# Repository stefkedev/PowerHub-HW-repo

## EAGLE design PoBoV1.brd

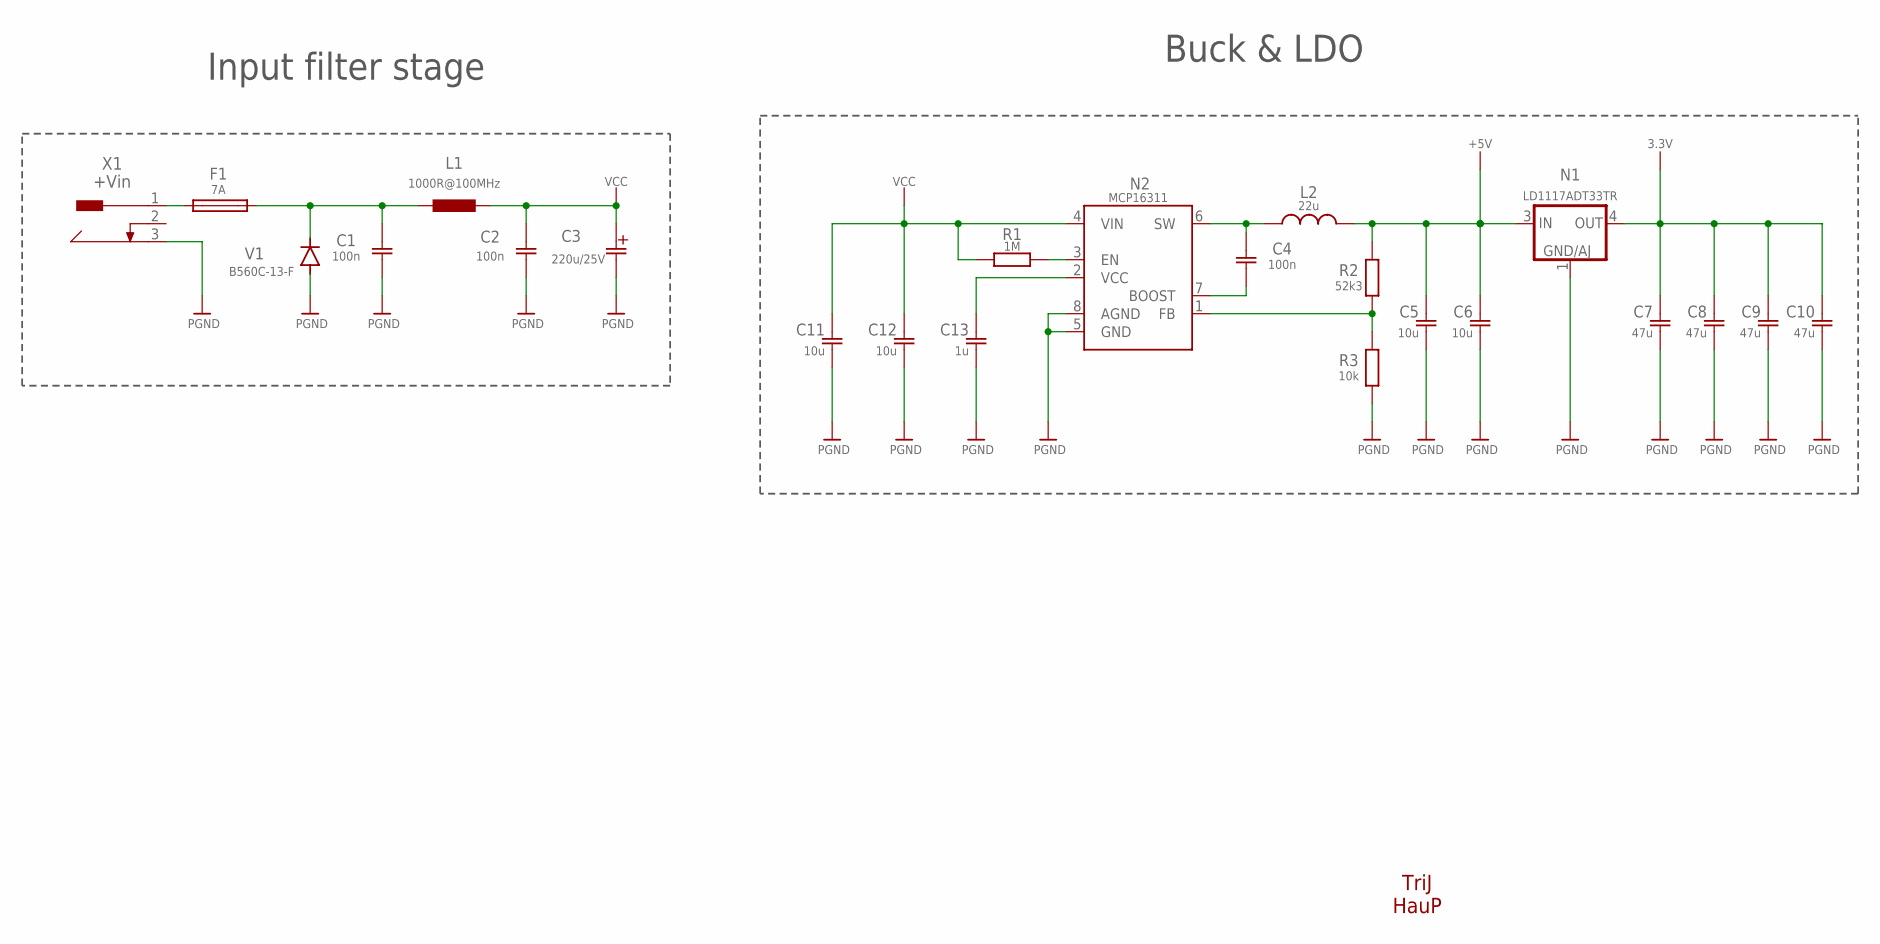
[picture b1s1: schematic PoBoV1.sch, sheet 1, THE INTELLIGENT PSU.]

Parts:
C1, C2, C4: 100n; C0805
C3: 220u/25V; E2,5-6L
C5, C6, C11, C12: 10u; C0805
C7, C8, C9, C10: 47u; C0805
C13: 1u; C0805
F1: 7A; TE5
L1: 1000R@100MHz; 0204/7@1
L2: 22u; WE-TPC_5818/5828
N1: LD1117ADT33TR; DPACK
N2: MCP16311; MSOP8
R1: 1M; R0805
R2: 52k3; R0805
R3: 10k; R0805
V1: B560C-13-F; SMC
X1: +Vin; DCJ0202

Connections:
+3.3: C7.1, C8.1, C9.1, C10.1, N1.4 (OUT); also elsewhere on the board
+5V: C5.1, C6.1, L2.2, N1.3 (IN), R2.2; also elsewhere on the board
unnamed: F1.1, X1.1
unnamed: C4.2, N2.7 (BOOST)
unnamed: N2.3 (EN), R1.2
unnamed: C1.1, F1.2, L1.1, V1.C
unnamed: C4.1, L2.1, N2.6 (SW)
unnamed: N2.1 (FB), R2.1, R3.2
unnamed: C13.1, N2.2 (VCC)
PGND: C1.2, C2.2, C3.-, C5.2, C6.2, C7.2, C8.2, C9.2, C10.2, C11.2, C12.2, C13.2, N1.1 (GND/ADJ), N2.5 (GND), N2.8 (AGND), R3.1, V1.A, X1.3; also elsewhere on the board
VCC: C2.1, C3.+, C11.1, C12.1, L1.2, N2.4 (VIN), R1.1; also elsewhere on the board

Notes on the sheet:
TriJ HauP
Input filter stage
Buck & LDO

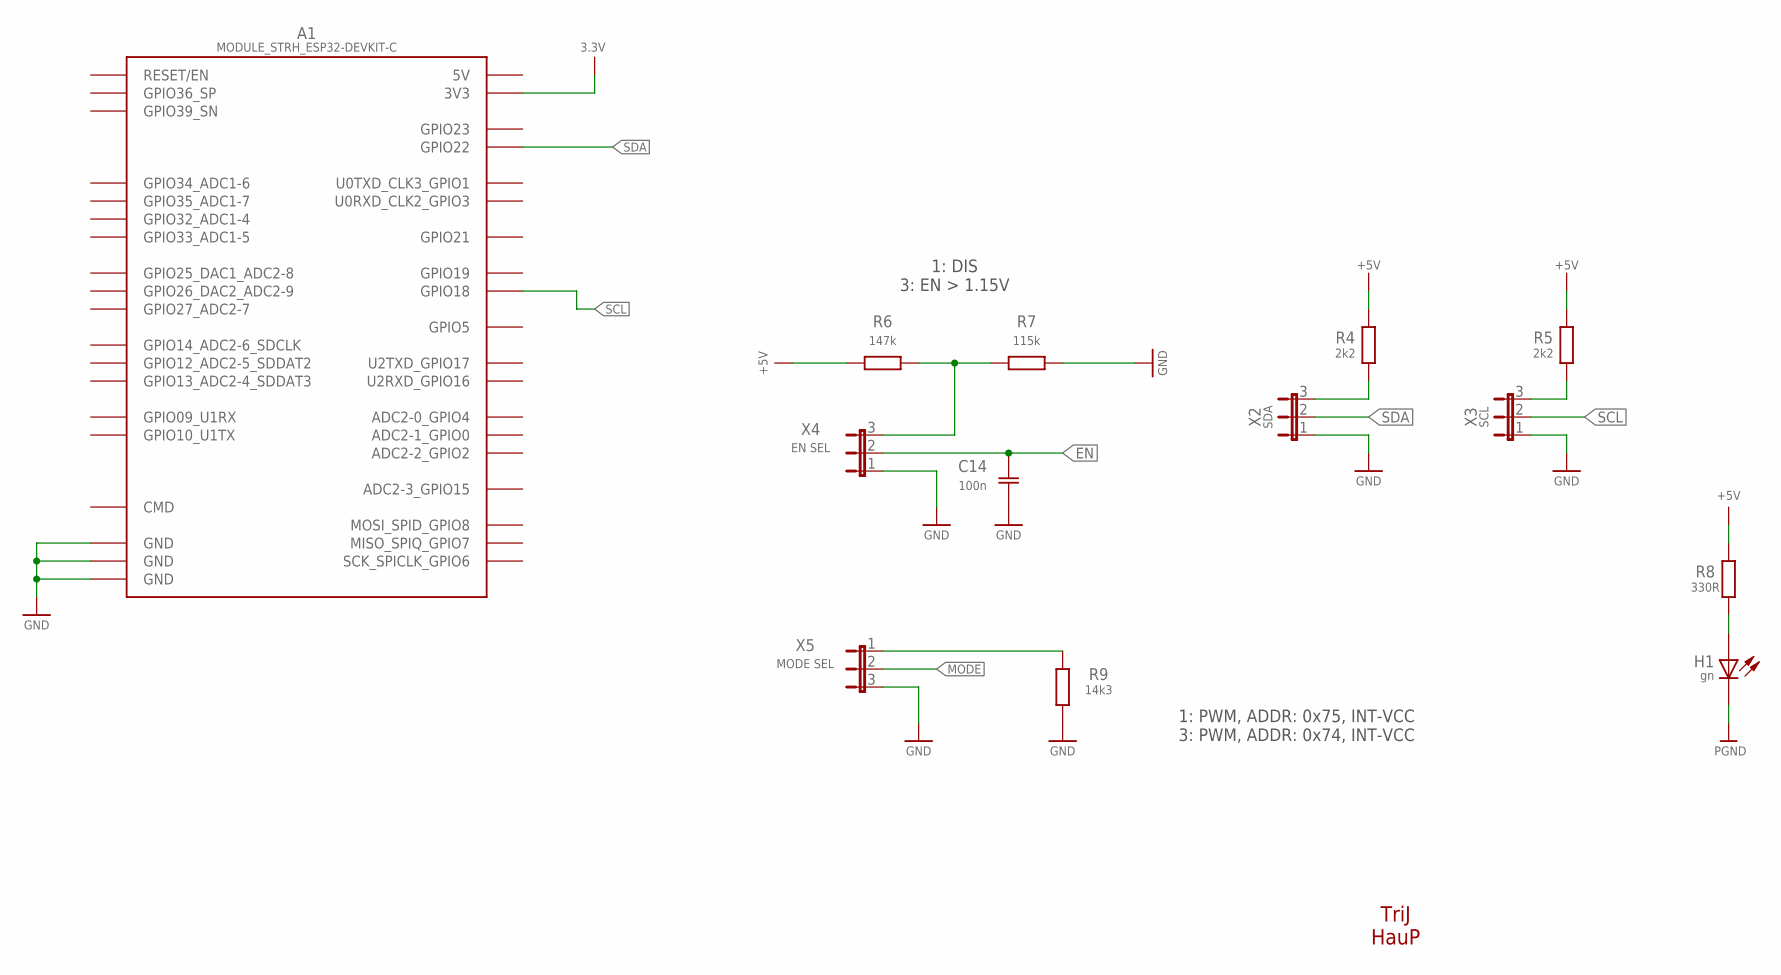
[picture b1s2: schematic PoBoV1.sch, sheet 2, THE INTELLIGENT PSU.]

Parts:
A1: MODULE_STRH_ESP32-DEVKIT-C; MODULE_STRH_DIL38-10_ESP
C14: 100n; C0805
H1: gn; CHIPLED_0805
R4, R5: 2k2; R0805
R6: 147k; R0805
R7: 115k; R0805
R8: 330R; R0805
R9: 14k3; R0805
X2: SDA; JUMPER_JP3
X3: SCL; JUMPER_JP3
X4: EN SEL; JUMPER_JP3
X5: MODE SEL; JUMPER_JP3

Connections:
+3.3: A1.3V3; also elsewhere on the board
+5V: R4.2, R5.2, R6.2, R8.2; also elsewhere on the board
EN: C14.1, X4.2; also elsewhere on the board
MODE: X5.2; also elsewhere on the board
unnamed: R6.1, R7.2, X4.3
unnamed: R4.1, X2.3
unnamed: R5.1, X3.3
unnamed: H1.A, R8.1
unnamed: R9.2, X5.1
PGND: A1.GND, A1.GND@1 (GND), A1.GND@2 (GND), C14.2, H1.C, R7.1, R9.1, X2.1, X3.1, X4.1, X5.3; also elsewhere on the board
SCL: A1.GPIO18, X3.2; also elsewhere on the board
SDA: A1.GPIO22, X2.2; also elsewhere on the board

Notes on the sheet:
1: PWM, ADDR: 0x75, INT-VCC 3: PWM, ADDR: 0x74, INT-VCC
1: DIS 3: EN > 1.15V
TriJ HauP

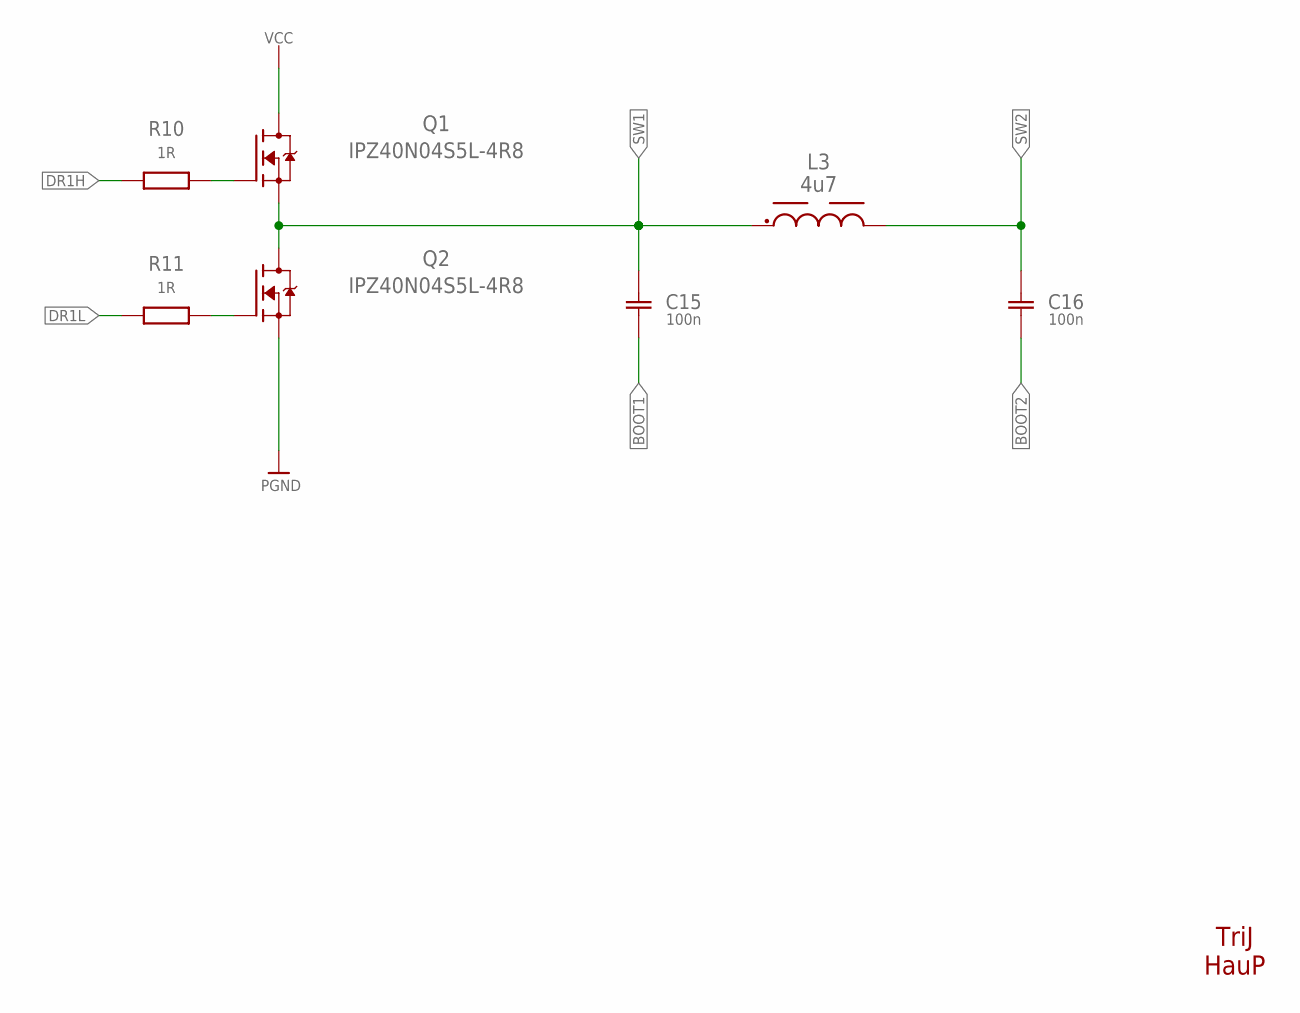
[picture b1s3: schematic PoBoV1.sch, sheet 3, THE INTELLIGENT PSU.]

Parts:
C15, C16: 100n; MYLIB_C0805
L3: 4u7; WE-PD_1280P
Q1, Q2: IPZ40N04S5L-4R8; TRANS_BSZ100N06LS3_G
R10, R11: 1R; R0805

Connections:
BOOT1: C15.2; also elsewhere on the board
BOOT2: C16.2; also elsewhere on the board
DR1H: R10.1; also elsewhere on the board
DR1L: R11.1; also elsewhere on the board
unnamed: Q1.4 (G), R10.2
unnamed: Q2.4 (G), R11.2
PGND: Q2.1 (S), Q2.2 (S), Q2.3 (S); also elsewhere on the board
SW1: C15.1, L3.1, Q1.1 (S), Q1.2 (S), Q1.3 (S), Q2.5_8 (D); also elsewhere on the board
SW2: C16.1, L3.2; also elsewhere on the board
VCC: Q1.5_8 (D); also elsewhere on the board

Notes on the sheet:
TriJ HauP

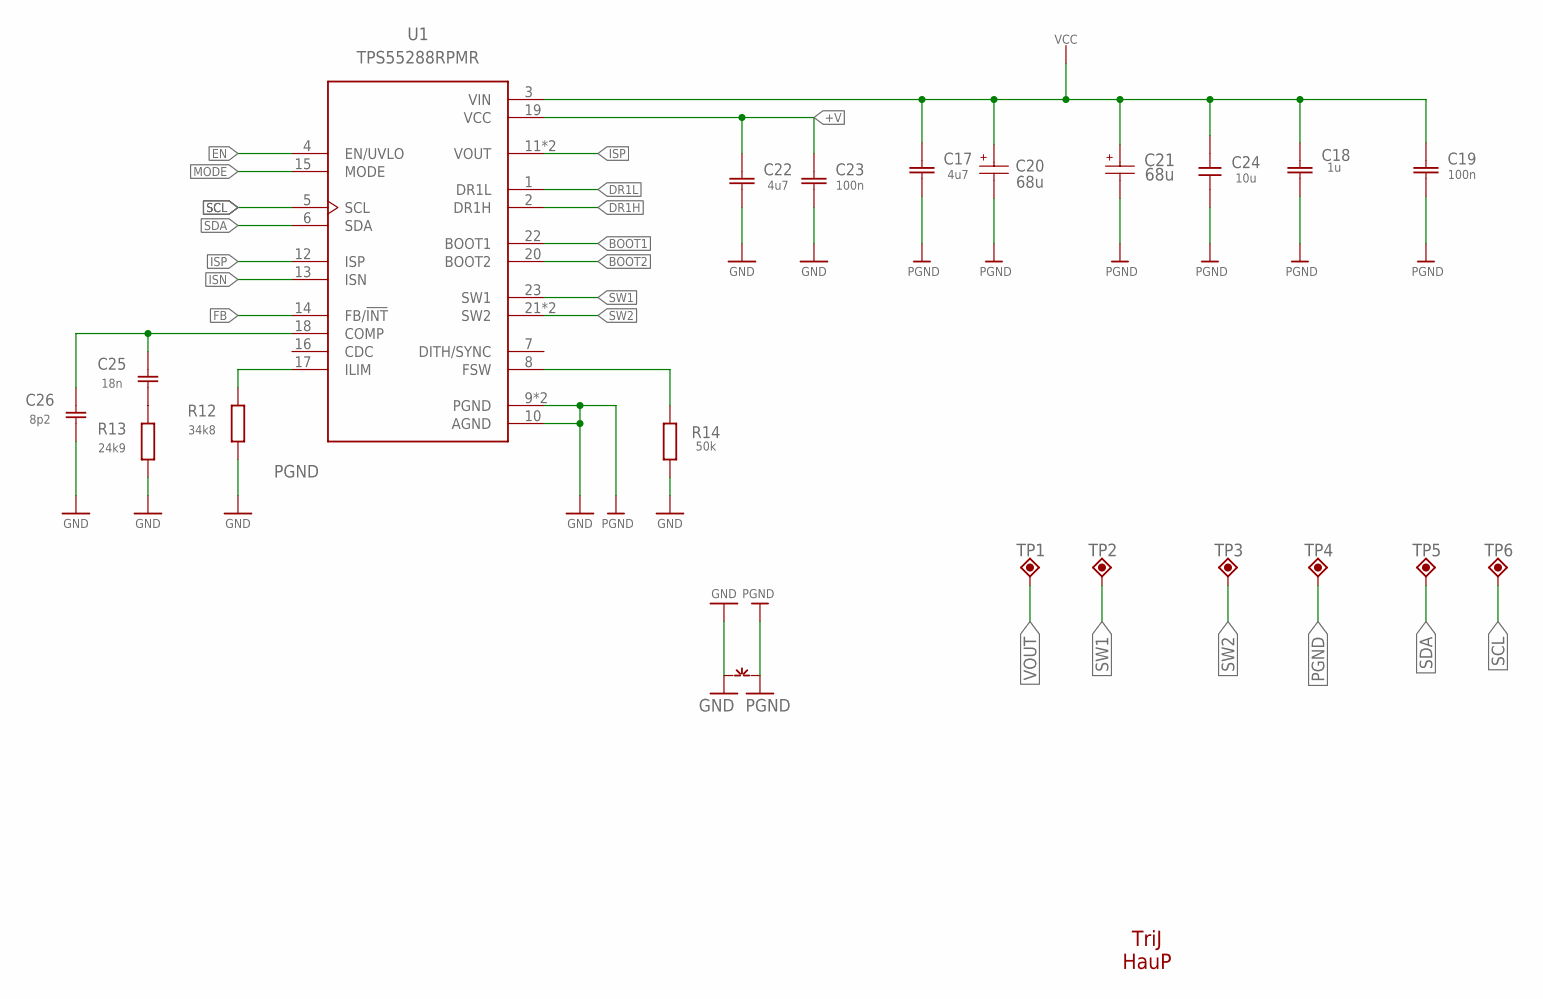
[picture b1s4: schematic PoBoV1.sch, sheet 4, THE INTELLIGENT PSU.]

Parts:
C17, C22: 4u7; MYRCL_C0603
C18: 1u; MYRCL_C0603K
C19: 100n; MYRCL_C0402
C20, C21: 68u; CAP_EEHZA1H680P
C23: 100n; MYRCL_C0603
C24: 10u; C1210
C25: 18n; MYLIB_C0805
C26: 8p2; MYLIB_C0805
R12: 34k8; R0805
R13: 24k9; R0805
R14: 50k; R0805
TP1, TP2, TP3, TP4, TP5, TP6: TPP-SMD-20SN; SMD-20SN
U1: TPS55288RPMR; IC_TPS55288RPMR
~NUDEV~1: GND-GNDA

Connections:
+V: C22.1, C23.1, U1.19 (VCC)
BOOT1: U1.22 (BOOT1); also elsewhere on the board
BOOT2: U1.20 (BOOT2); also elsewhere on the board
DR1H: U1.2 (DR1H); also elsewhere on the board
DR1L: U1.1 (DR1L); also elsewhere on the board
EN: U1.4 (EN/UVLO); also elsewhere on the board
FB: U1.14 (FB/!INT)
ISN: U1.13 (ISN); also elsewhere on the board
ISP: U1.11 (VOUT), U1.12 (ISP), U1.26 (VOUT); also elsewhere on the board
MODE: U1.15 (MODE); also elsewhere on the board
unnamed: C25.2, R13.2
unnamed: C25.1, C26.1, U1.18 (COMP)
unnamed: R14.1, U1.8 (FSW)
unnamed: R12.2, U1.17 (ILIM)
PGND: C17.2, C18.2, C19.2, C20.2, C21.2, C22.2, C23.2, C24.2, C26.2, R12.1, R13.1, R14.2, TP4.TP, U1.9 (PGND), U1.10 (AGND), U1.24 (PGND), ~NUDEV~1.GND, ~NUDEV~1.PGND (GNDA); also elsewhere on the board
SCL: TP6.TP, U1.5 (SCL); also elsewhere on the board
SDA: TP5.TP, U1.6 (SDA); also elsewhere on the board
SW1: TP2.TP, U1.23 (SW1); also elsewhere on the board
SW2: TP3.TP, U1.21 (SW2), U1.25 (SW2); also elsewhere on the board
VCC: C17.1, C18.1, C19.1, C20.1, C21.1, C24.1, U1.3 (VIN); also elsewhere on the board
VOUT: TP1.TP; also elsewhere on the board

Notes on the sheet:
TriJ HauP

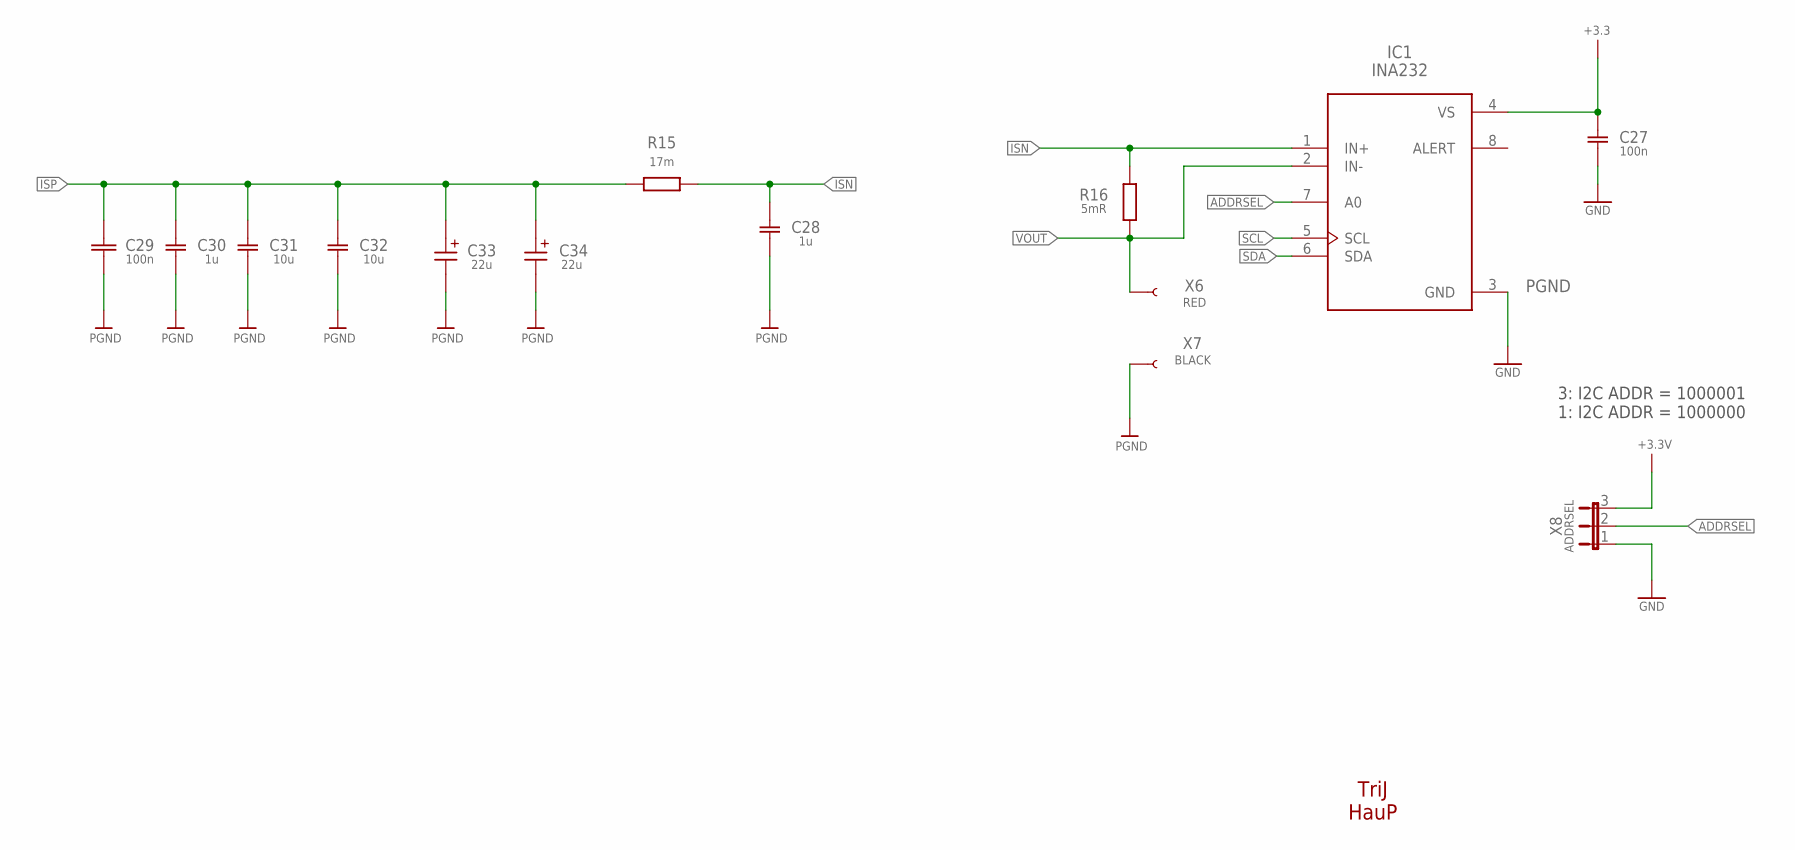
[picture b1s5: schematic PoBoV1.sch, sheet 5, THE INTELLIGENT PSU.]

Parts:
C27: 100n; MYLIB_C0805
C28, C30: 1u; MYLIB_C0805
C29: 100n; MYRCL_C0402
C31, C32: 10u; MYLIB_C0805
C33, C34: 22u; PANASONIC_G
IC1: INA232; SOT65P280X110-8N
R15: 17m; R0805
R16: 5mR; RCL_STRH_R0805
X6: RED; BANANAJACK
X7: BLACK; BANANAJACK
X8: ADDRSEL; JUMPER_JP3

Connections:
+3.3: C27.1, IC1.4 (VS); also elsewhere on the board
+3.3V: X8.3
ADDRSEL: IC1.7 (A0), X8.2
ISN: C28.1, IC1.1 (IN+), R15.1, R16.2; also elsewhere on the board
ISP: C29.1, C30.1, C31.1, C32.1, C33.+, C34.+, R15.2; also elsewhere on the board
PGND: C27.2, C28.2, C29.2, C30.2, C31.2, C32.2, C33.-, C34.-, IC1.3 (GND), X7.P$1, X8.1; also elsewhere on the board
SCL: IC1.5 (SCL); also elsewhere on the board
SDA: IC1.6 (SDA); also elsewhere on the board
VOUT: IC1.2 (IN-), R16.1, X6.P$1; also elsewhere on the board

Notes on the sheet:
3: I2C ADDR = 1000001 1: I2C ADDR = 1000000
TriJ HauP

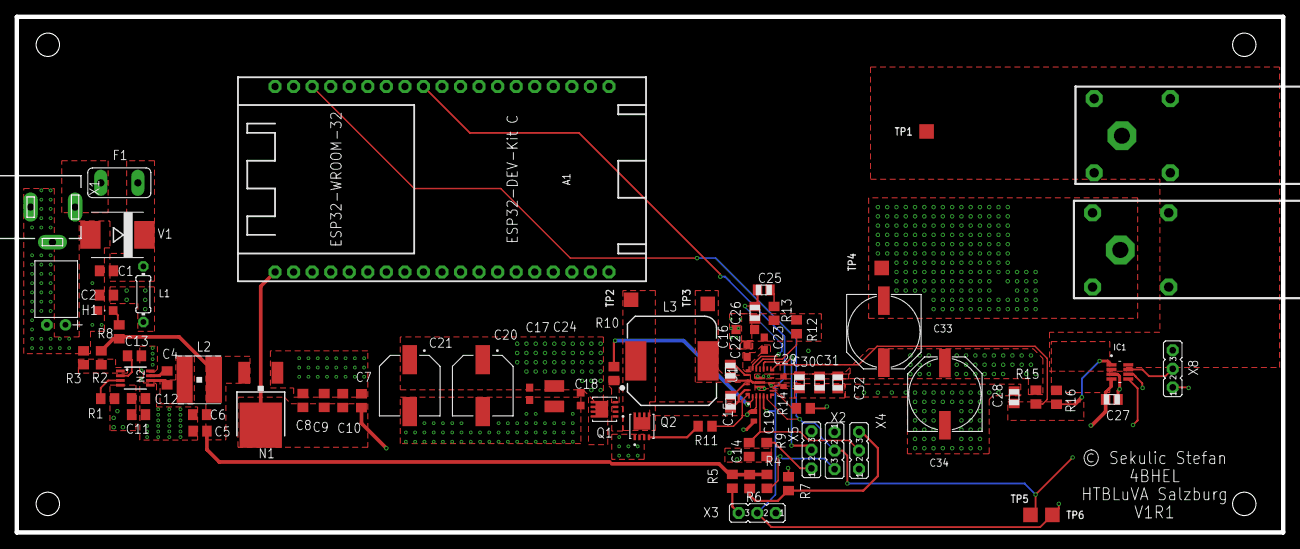
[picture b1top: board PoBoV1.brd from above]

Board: 4 copper layers, 173.4 x 70.6 mm, 81 parts (0 on the bottom side), 37 nets.

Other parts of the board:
BOM: BOM
FABRICATION: FABRIACTION
MEASURE: MEASURE

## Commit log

2024-12-29 Removed savefiles
2024-12-29 Made some traces thiccer and added bananaplug
2024-12-29 Add files via upload
    Added testpoints and banana jacks
2024-12-29 Fixed routing, connected testpoints
2024-12-29 OIDA
2025-01-01 Add files via upload
    Final Version that includes whole layout revamp

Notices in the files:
PoBoV1.brd:
© Sekulic Stefan
parts and their libraries:
testpoint: Copyright (C) 2008, Bob Starr
